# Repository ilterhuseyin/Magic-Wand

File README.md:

🪄 Magic Wand (POV Display) - PCB Design
This repository contains the hardware design files for the Magic Wand project, inspired by Andre LaMothe's "Crash Course Electronics and PCB Design".

The Magic Wand is a classic Persistence of Vision (POV) device. When the PCB is waved through the air, the precisely timed LED strobing creates the illusion of floating text or graphics.

🛠 Project Structure
The repository is organized to provide everything needed for manufacturing and further development:

Magic Wand.kicad_sch: The schematic diagram showing the circuit architecture.

Magic Wand.kicad_pcb: The physical board layout, optimized for a handheld wand form factor.

Magic Wand.kicad_pro: The KiCad project management file.

Manufacturing/: This folder contains the necessary output files (such as Gerbers) for PCB fabrication.

🚀 Technical Details
Software: Designed using KiCad.

Concept: Utilizes the POV (Persistence of Vision) effect.

Design Focus: Compact handheld design, signal integrity for high-speed LED switching, and ease of assembly.

💡 Usage
To use these files:

Open the .kicad_pro file in KiCad to view or modify the schematics and PCB layout.

Use the files in the Manufacturing/ directory to order the board from any PCB manufacturer.

🎓 Acknowledgments
This project is a hardware implementation based on the educational materials provided by Andre LaMothe in his electronics and PCB design course.

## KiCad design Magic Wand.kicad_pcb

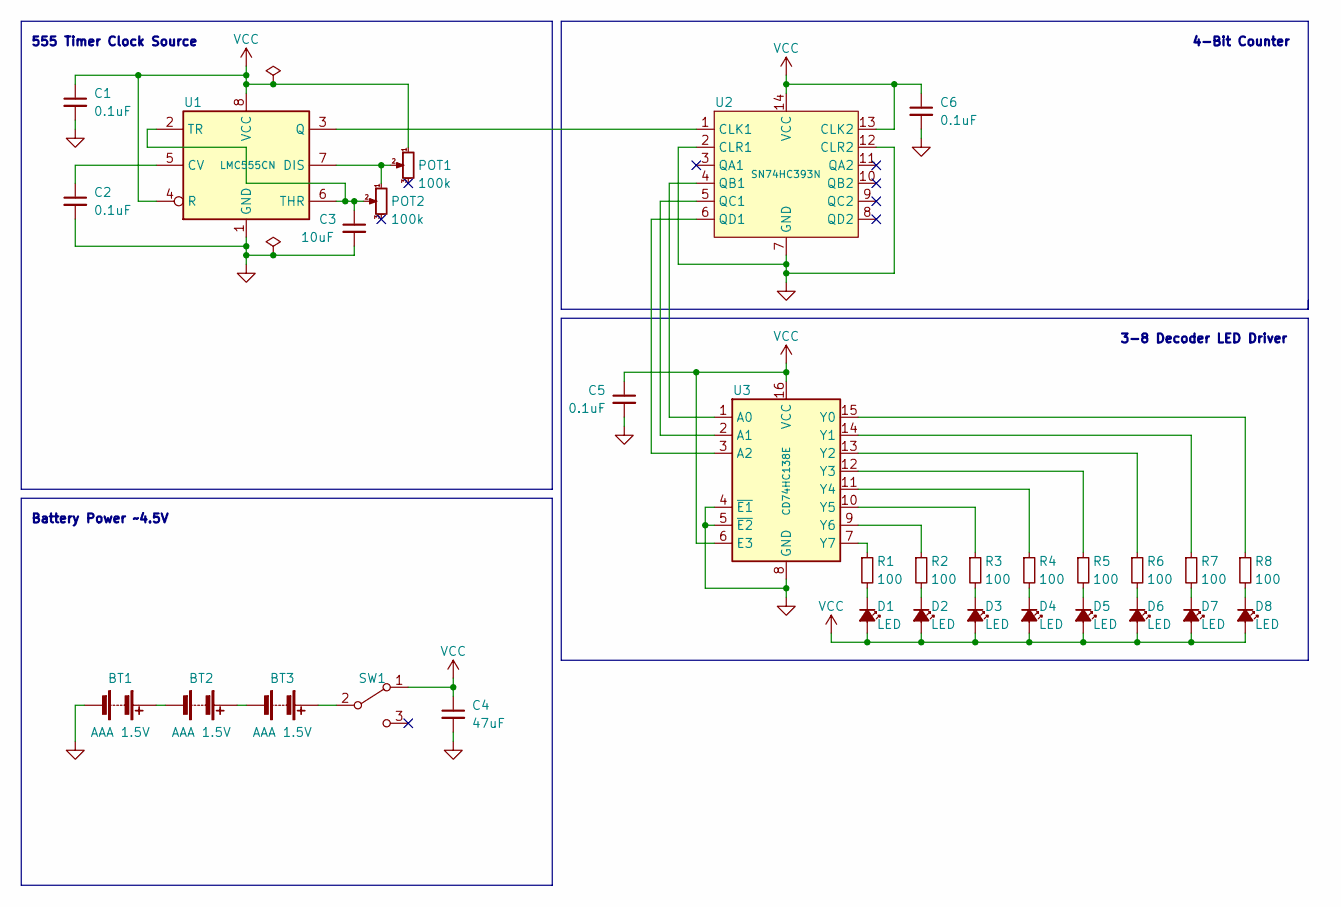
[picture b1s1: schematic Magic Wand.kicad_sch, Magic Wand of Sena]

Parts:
BT1, BT2, BT3: AAA 1.5V; BatteryHolder_Keystone_2466_1xAAA
C1, C2, C5, C6: 0.1uF; C_Disc_D5.0mm_W2.5mm_P2.50mm
C3: 10uF; C_Disc_D5.0mm_W2.5mm_P2.50mm
C4: 47uF; C_Radial_D6.3mm_H7.0mm_P2.50mm
D1, D2, D3, D4, D5, D6, D7, D8: LED; LED_D5.0mm
POT1, POT2: 100k; Potentiometer_Vishay_T73YP_Vertical
R1, R2, R3, R4, R5, R6, R7, R8: 100; R_Axial_DIN0207_L6.3mm_D2.5mm_P7.62mm_Horizontal
SW1: SW_SPDT; JST_EH_B3B-EH-A_1x03_P2.50mm_Vertical
U1: LMC555CN; DIP-8_W7.62mm
U2: SN74HC393N; DIP-14_W7.62mm
U3: CD74HC138E; DIP-16_W7.62mm

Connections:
GND: BT1.2 (-), C1.2, C2.2, C3.2, C4.2, C5.2, C6.2, U1.1 (GND), U2.2 (CLR1), U2.7 (GND), U2.12 (CLR2), U3.4 (~E1), U3.5 (~E2), U3.8 (GND)
unnamed: BT1.1 (+), BT2.2 (-)
unnamed: BT2.1 (+), BT3.2 (-)
unnamed: BT3.1 (+), SW1.2 (B)
unnamed: C2.1, U1.5 (CV)
unnamed: D1.1 (K), R1.2
unnamed: D2.1 (K), R2.2
unnamed: D3.1 (K), R3.2
unnamed: D4.1 (K), R4.2
unnamed: D5.1 (K), R5.2
unnamed: D6.1 (K), R6.2
unnamed: D7.1 (K), R7.2
unnamed: D8.1 (K), R8.2
unnamed: POT1.2, POT2.1, U1.7 (DIS)
unnamed: C3.1, POT2.2, U1.2 (TR), U1.6 (THR)
unnamed: R1.1, U3.7 (Y7)
unnamed: R2.1, U3.9 (Y6)
unnamed: R3.1, U3.10 (Y5)
unnamed: R4.1, U3.11 (Y4)
unnamed: R5.1, U3.12 (Y3)
unnamed: R6.1, U3.13 (Y2)
unnamed: R7.1, U3.14 (Y1)
unnamed: R8.1, U3.15 (Y0)
unnamed: U1.3 (Q), U2.1 (CLK1)
unnamed: U2.4 (QB1), U3.1 (A0)
unnamed: U2.5 (QC1), U3.2 (A1)
unnamed: U2.6 (QD1), U3.3 (A2)
VCC: C1.1, C4.1, C5.1, C6.1, D1.2 (A), D2.2 (A), D3.2 (A), D4.2 (A), D5.2 (A), D6.2 (A), D7.2 (A), D8.2 (A), POT1.1, SW1.1 (A), U1.4 (R), U1.8 (VCC), U2.13 (CLK2), U2.14 (VCC), U3.6 (E3), U3.16 (VCC)

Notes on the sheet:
555 Timer Clock Source
3-8 Decoder LED Driver
Battery Power ~4.5V
4-Bit Counter

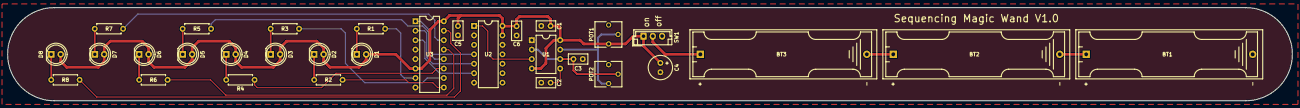
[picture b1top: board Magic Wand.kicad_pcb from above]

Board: 2 copper layers, 345.0 x 25.0 mm, 31 parts (0 on the bottom side), 28 nets.

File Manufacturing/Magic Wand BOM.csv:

"Source:","C:\Users\hueseyin.ilter\Documents\KiCad\6.0\projects\Magic Wand\Magic Wand.kicad_sch"
"Date:","11/14/2022 3:38:32 PM"
"Tool:","Eeschema (6.0.7)"
"Generator:","C:\Program Files\KiCad\6.0\bin\scripting\plugins/bom_csv_grouped_by_value_with_fp.py"
"Component Count:","31"
"Ref","Qnty","Value","Cmp name","Footprint","Description","Vendor"
"BT1, BT2, BT3, ","3","AAA 1.5V","Battery","Battery:BatteryHolder_Keystone_2466_1xAAA","Multiple-cell battery",""
"C1, C2, C5, C6, ","4","0.1uF","C_Small","Capacitor_THT:C_Disc_D5.0mm_W2.5mm_P2.50mm","Unpolarized capacitor, small symbol",""
"C3, ","1","10uF","C_Small","Capacitor_THT:C_Disc_D5.0mm_W2.5mm_P2.50mm","Unpolarized capacitor, small symbol",""
"C4, ","1","47uF","C_Small","Capacitor_THT:C_Radial_D6.3mm_H7.0mm_P2.50mm","Unpolarized capacitor, small symbol",""
"D1, D2, D3, D4, D5, D6, D7, D8, ","8","LED","LED_Small_Filled","LED_THT:LED_D5.0mm","Light emitting diode, small symbol, filled shape",""
"POT1, POT2, ","2","100k","R_Potentiometer_Small","Potentiometer_THT:Potentiometer_Vishay_T73YP_Vertical","Potentiometer",""
"R1, R2, R3, R4, R5, R6, R7, R8, ","8","100","R_Small","Resistor_THT:R_Axial_DIN0207_L6.3mm_D2.5mm_P7.62mm_Horizontal","Resistor, small symbol",""
"SW1, ","1","SW_SPDT","SW_SPDT","Connector_JST:JST_EH_B3B-EH-A_1x03_P2.50mm_Vertical","Switch, single pole double throw",""
"U1, ","1","LMC555CN","LMC555xN","Package_DIP:DIP-8_W7.62mm","CMOS Timer, 555 compatible, PDIP-8",""
"U2, ","1","SN74HC393N","74HC393","Package_DIP:DIP-14_W7.62mm","",""
"U3, ","1","CD74HC138E","CD74AC238","Package_DIP:DIP-16_W7.62mm","3-to-8 line decoder/multiplexer, SOIC-16",""

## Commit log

2026-05-04 Revise README.md with project details and usage
    Expanded project description and added details about the project structure, technical details, usage instructions, and acknowledgments.
